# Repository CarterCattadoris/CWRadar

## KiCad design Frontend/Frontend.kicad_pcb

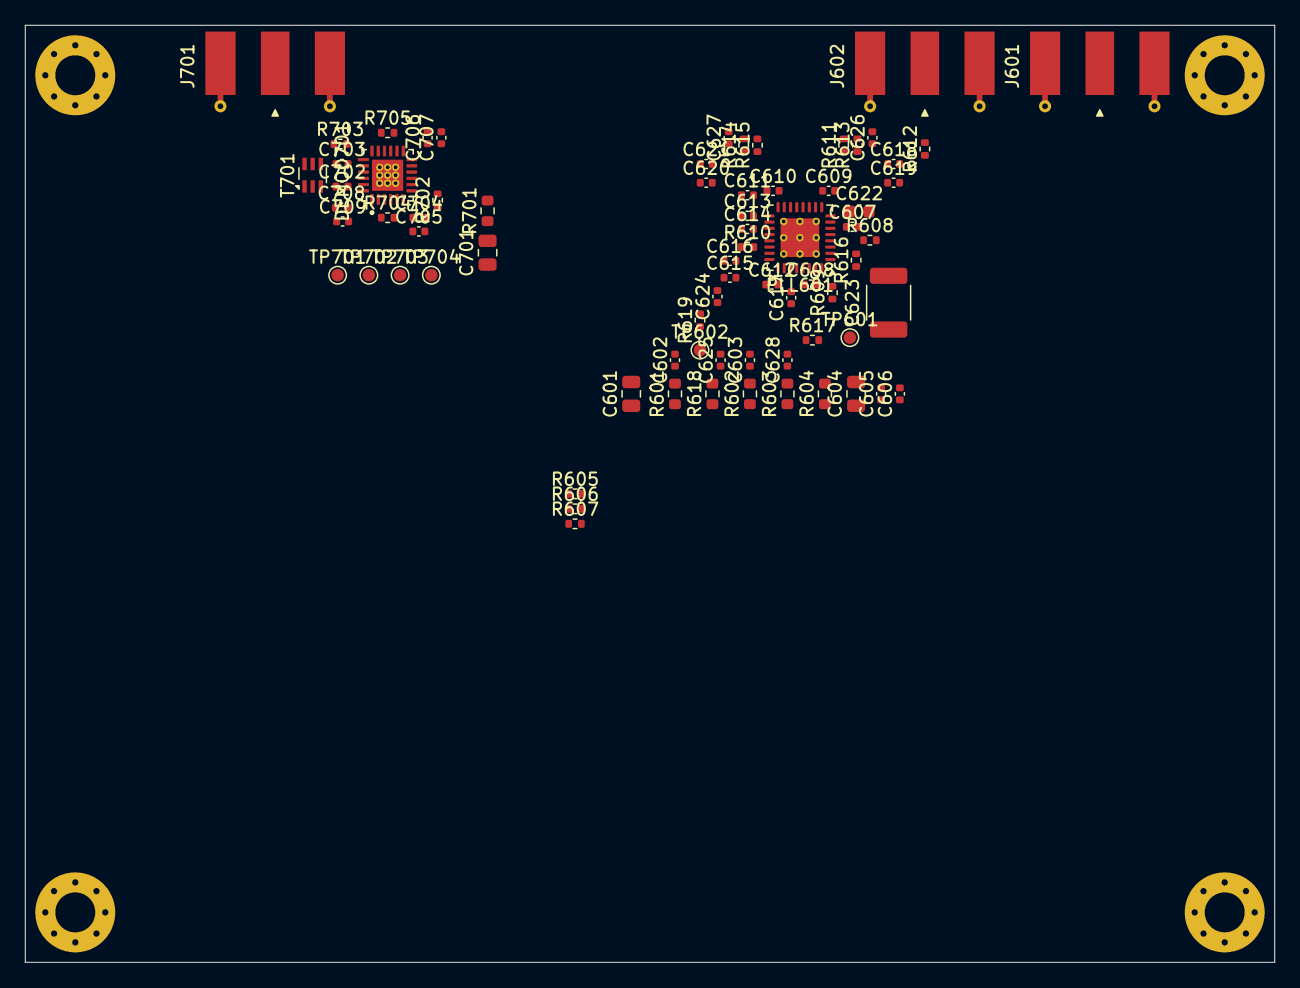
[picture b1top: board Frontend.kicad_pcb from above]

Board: 4 copper layers, 100.0 x 75.0 mm, 77 parts (0 on the bottom side), 42 nets, no tracks yet.

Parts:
C601, C604, C701: 10u; C_0805_2012Metric
C602, C603, C607, C608, C609, C611, C612, C613, C614, C615, C616, C625, C628: 1u; C_0402_1005Metric
C605, C705, C707, C709: 100n; C_0402_1005Metric
C606: 10n; C_0402_1005Metric
C610, C618, C619, C620, C621, C626, C627, C702, C703: TBD; C_0402_1005Metric
C617: 1n; C_0402_1005Metric
C622: 12n; C_0603_1608Metric
C623: 100n; C_Panasonic_ECHU_E2
C624: 820p; C_0402_1005Metric
C704, C706, C708: 100p; C_0402_1005Metric
DEMOD701: ADL5380; 24-WFQFN
J601: TX SMA; SMA_Molex_73251-1153_EdgeMount_Horizontal
J602: MON SMA; SMA_Molex_73251-1153_EdgeMount_Horizontal
J701: RX SMA; SMA_Molex_73251-1153_EdgeMount_Horizontal
MH1101, MH1102, MH1103, MH1104: M3; MountingHole_3.2mm_M3_Pad_Via
PLL601: MAX2871ETJ_T; TQFN-32-1EP_5x5mm_P0.5mm_EP3.1x3.1mm_ThermalVias0.3
R601, R602, R603, R618, R701: 0R; R_0603_1608Metric
R604: 10; R_0603_1608Metric
R605, R606, R607: 47; R_0402_1005Metric
R608, R609, R619: 100k; R_0402_1005Metric
R610: 5k1; R_0402_1005Metric
R611, R612, R613, R614, R615: 49R9; R_0402_1005Metric
R616: 120; R_0402_1005Metric
R617: 249; R_0402_1005Metric
R702: 0R; R_0402_1005Metric
R703: DNP (open >5 GHz); R_0402_1005Metric
R704, R705: DNP — diff load ≥500 Ω; R_0402_1005Metric
T701: 5400BL15B050; Balun_Johanson_5400BL15B050E
TP601: LD; TestPoint_Pad_D1.0mm
TP602: TUNE; TestPoint_Pad_D1.0mm
TP701: I_P; TestPoint_Pad_D1.0mm
TP702: I_N; TestPoint_Pad_D1.0mm
TP703: Q_N; TestPoint_Pad_D1.0mm
TP704: Q_P; TestPoint_Pad_D1.0mm

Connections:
+3V3_SYN: C601.1, R601.1, R602.1, R603.1, R604.1, R618.1
+3V3_SYN_DIG: C608.1, C612.1, C628.1, PLL601.28, PLL601.32, R603.2
+3V3_SYN_PLL: C603.1, C607.1, C609.1, PLL601.6, PLL601.10, R602.2
+3V3_SYN_REF: C604.1, C605.1, C606.1, R604.2
+3V3_SYN_RF: C602.1, C610.1, C611.1, C626.1, C627.1, PLL601.16, R601.2, R611.1, R613.1, R614.1, R615.1
+3V3_SYN_VCO: C613.1, C625.1, PLL601.17, R618.2
+5V_DEMOD: C701.1, C704.1, C705.1, C706.1, C707.1, C708.1, C709.1, DEMOD701.6, DEMOD701.13, DEMOD701.24, R701.2, R703.1
/Baseband_I/IN_N: DEMOD701.4, R704.2, TP702.1
/Baseband_I/IN_P: DEMOD701.3, R704.1, TP701.1
/Baseband_Q/IN_N: DEMOD701.15, R705.1, TP703.1
/Baseband_Q/IN_P: DEMOD701.16, R705.2, TP704.1
/Receiver/DEMOD_ADJ: DEMOD701.19, R703.2
/Receiver/DEMOD_ENBL: DEMOD701.7, R702.1
/Receiver/DEMOD_RFIN: C703.2, DEMOD701.21
/Receiver/DEMOD_RFIP: C702.2, DEMOD701.22
/Receiver/LO_N: C620.2, DEMOD701.9
/Receiver/LO_P: C621.2, DEMOD701.10
/Receiver/RX_BAL_N: C703.1, T701.4
/Receiver/RX_BAL_P: C702.1, T701.3
/Receiver/RX_RF: J701.1, T701.1
/Synthesizer/BIAS_FILT: C616.1, PLL601.23
/Synthesizer/CP_OUT: C622.1, PLL601.7, R616.1, R617.1
/Synthesizer/LF_C2: C623.1, R616.2
/Synthesizer/MON_RF: C618.2, J602.1, R612.1
/Synthesizer/NOISE_FILT: C614.1, PLL601.19
/Synthesizer/REF_IN: C617.2, PLL601.29
/Synthesizer/REG: C615.1, PLL601.24
/Synthesizer/RFOUTA_N: C618.1, PLL601.13, R611.2
/Synthesizer/RFOUTA_P: C619.1, PLL601.12, R613.2
/Synthesizer/RFOUTB_N: C620.1, PLL601.15, R614.2
/Synthesizer/RFOUTB_P: C621.1, PLL601.14, R615.2
/Synthesizer/RSET: PLL601.22, R610.1
/Synthesizer/SYN_CE: PLL601.4, R608.1
/Synthesizer/SYN_LD: PLL601.25, TP601.1
/Synthesizer/SYN_LE_R: PLL601.3, R607.2
/Synthesizer/SYN_MOSI_R: PLL601.2, R606.2
/Synthesizer/SYN_RFOUT_EN: PLL601.26, R609.1
/Synthesizer/SYN_SCK_R: PLL601.1, R605.2
/Synthesizer/TUNE: C624.1, PLL601.20, R617.2, R619.1
/Synthesizer/TUNE_TP: R619.2, TP602.1
/Synthesizer/TX_RF: C619.2, J601.1
GND: C601.2, C602.2, C603.2, C604.2, C605.2, C606.2, C607.2, C608.2, C609.2, C610.2, C611.2, C612.2, C613.2, C614.2, C615.2, C616.2, C622.2, C623.2, C624.2, C625.2, C626.2, C627.2, C628.2, C701.2, C704.2, C705.2, C706.2, C707.2, C708.2, C709.2, DEMOD701.1, DEMOD701.2, DEMOD701.5, DEMOD701.8, DEMOD701.11, DEMOD701.14, DEMOD701.17, DEMOD701.18, DEMOD701.20, DEMOD701.23, DEMOD701.25, DEMOD701.25_1, DEMOD701.25_2, DEMOD701.25_3, DEMOD701.25_4, DEMOD701.25_5, DEMOD701.25_6, DEMOD701.25_7, DEMOD701.25_8, DEMOD701.25_9, J601.2, J602.2, J701.2, MH1101.1, MH1102.1, MH1103.1, MH1104.1, PLL601.8, PLL601.9, PLL601.11, PLL601.18, PLL601.21, PLL601.27, PLL601.31, PLL601.33, R608.2, R609.2, R610.2, R612.2, R702.2, T701.2, T701.5

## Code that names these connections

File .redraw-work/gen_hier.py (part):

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    vpart(ref, "cwradar:100k", 40.64, y + 3.81)
    gnd(40.64, y + 7.62)
YLD = 184.15 + SH
hlabel("SYN_LD", 33.02, YLD, 180, "output")
wire((33.02, YLD), (48.26, YLD))
place("TP1", "Connector:TestPoint", 48.26, YLD, value="LD",
      fp="TestPoint:TestPoint_Pad_D1.0mm",
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
# ============================================================== LOOP FILTER
Y0 = 214.63 + SH
label("CP_OUT", 22.86, Y0, 180)
wire((22.86, Y0), (52.07, Y0))
vpart("C22", "cwradar:12n", 33.02, Y0 + 3.81); gnd(33.02, Y0 + 7.62)
vpart("R16", "cwradar:120", 43.18, Y0 + 3.81)
wire((43.18, Y0 + 7.62), (43.18, Y0 + 10.16))
label("LF_C2", 43.18, Y0 + 8.89, 90, small=True)
vpart("C23", "cwradar:100n_PPS", 43.18, Y0 + 13.97); gnd(43.18, Y0 + 17.78)
hpart("R17", "cwradar:249", 55.88, Y0)
wire((59.69, Y0), (78.74, Y0))
vpart("C24", "cwradar:820p", 66.04, Y0 + 3.81); gnd(66.04, Y0 + 7.62)
label("TUNE", 73.66, Y0, 0)
# TUNE probe point: 100k keeps probe capacitance off the loop filter
vpart("R19", "cwradar:100k", 78.74, Y0 + 3.81,
      extra={"Note": "Isolates probe capacitance from loop filter. Place R at the TUNE node."})
wire((78.74, Y0 + 7.62), (78.74, Y0 + 10.16))
label("TUNE_TP", 78.74, Y0 + 8.89, 90, small=True)
place("TP2", "Connector:TestPoint", 78.74, Y0 + 10.16, rot=180, value="TUNE",
      fp="TestPoint:TestPoint_Pad_D1.0mm",
      fields={"Reference": (81.28, Y0 + 12.7, 0, False, "right"), "Value": (81.28, Y0 + 15.24, 0, False, "right")})
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R = P["6"][0]   # right pin x

# left-side control/status labels
for pin, net in [("4", "SYN_CE"), ("1", "SYN_SCK_R"), ("2", "SYN_MOSI_R"),
                 ("3", "SYN_LE_R"), ("20", "TUNE")]:
    label(net, *P[pin], 180)
NCS.append(P["5"])
# right-side labels
for pin, net in [("26", "SYN_RFOUT_EN"), ("7", "CP_OUT"), ("25", "SYN_LD"),
                 ]:
    label(net, *P[pin], 0)
hlabel("SYN_MISO", *P["30"], 0, "output")
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
# VCO / bias decoupling and RSET: staircase down-left
YB = 165.1
for pin, cref, part, cx, net in [("23", "C16", "cwradar:1u", 127.0, "BIAS_FILT"),
                                 ("24", "C15", "cwradar:1u", 116.84, "REG"),
                                 ("19", "C14", "cwradar:1u", 106.68, "NOISE_FILT"),
                                 ("22", "R10", "cwradar:5k1", 96.52, "RSET")]:
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hpart("C17", "cwradar:1n", 125.73, ry,
      fields={"Reference": (125.73, ry - 2.794, 90, False), "Value": (125.73, ry + 3.175, 90, False)})
wire(P["29"], (129.54, ry))
label("REF_IN", 130.81, ry, 0, small=True)
label("REF_25M", 121.92, ry, 180)

# reference TCXO placeholder (part TBD), on the RC-filtered +3V3_SYN_REF branch
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    hpart(cref, "Device:C", DCB, Y, value="TBD", fp="Capacitor_SMD:C_0402_1005Metric")
    if net == "RFOUTA_P":
        wire((DCB + 3.81, Y), (J - 5.08, Y))
        label("TX_RF", DCB + 5.08, Y, 0, small=True)
        place("J1", "Connector:Conn_Coaxial", J, Y, value="TX SMA", fp="Connector_Coaxial:SMA_Molex_73251-1153_EdgeMount_Horizontal", extra={"Manufacturer": "Molex", "Mfg Part #": "73251-1153", "Description": "SMA jack, edge mount, 1.6 mm PCB"},
              fields={"Reference": (J + 3.81, Y - 2.54, 0, False, "left"),
                      "Value": (J + 3.81, Y, 0, False, "left")})
        gnd(J, Y + 5.08)
    elif net == "RFOUTA_N":
        wire((DCB + 3.81, Y), (J - 5.08, Y))
        label("MON_RF", DCB + 5.08, Y, 0, small=True)
        vpart("R12", "cwradar:49R9", 238.76, Y + 3.81); gnd(238.76, Y + 7.62)
        place("J2", "Connector:Conn_Coaxial", J, Y, value="MON SMA",
              fp="Connector_Coaxial:SMA_Molex_73251-1153_EdgeMount_Horizontal", dnp=True, extra={"Manufacturer": "Molex", "Mfg Part #": "73251-1153", "Description": "SMA jack, edge mount, 1.6 mm PCB"},
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
# ===================================================================== notes
text("MAX2871 NOTES (DS Rev 4)\n"
     "- One 1u 10V X5R 0402 on every supply pin (C7-C9, C11-C13), branch caps C2/C3 and NOISE_FILT/BIAS_FILT/REG (C14-C16).\n"
     "  Place each 1u directly at its pin, own GND via at or in the pad. Check the part's DC-bias curve at 3.3V; no Y5V.\n"
     "- C10: C0G 0402 on VCC_RF, series-resonant at 5.8 GHz when mounted (~1-3 pF, from vendor S-params), closest to pin 16.\n"
     "- C18-C21 DC blocks: 0402 C0G near series resonance at 5.8 GHz. R5-R7 47R series: place at the ESP32 end.\n"
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          fields={"Reference": (129.54, 114.3, 0, False), "Value": (129.54, 116.84, 0, False)})
assert T["4"] == (134.62, YN) and T["3"] == (134.62, YP), T
wire(J["1"], T["1"])
label("RX_RF", 109.22, YP, 0, small=True)
gx2, gy2 = T["2"]  # GND pins face up on the mirrored balun
wire((gx2, gy2), (gx2, gy2 - 2.54), (gx2 - 5.08, gy2 - 2.54), (gx2 - 5.08, gy2))
gnd(gx2 - 5.08, gy2)
# balanced polarity chosen for a crossing-free layout (RF inversion flips I and Q together)
for tp, bal, cref, dem, pin in [("3", "RX_BAL_P", "C2", "DEMOD_RFIP", "22"),
                                ("4", "RX_BAL_N", "C3", "DEMOD_RFIN", "21")]:
    y = T[tp][1]
    wire(T[tp], (153.67, y))
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
# LO in: already AC-coupled on the synthesizer sheet (C620/C621). LO_P -> LOIN so the pair
# routes without crossing; LO inversion flips I and Q together, so the Doppler sign is unchanged.
for pin, lo in [("10", "LO_P"), ("9", "LO_N")]:
    px, py = D[pin]
    hlabel(lo, 160.02, py, 180, "input")
    wire((160.02, py), (px, py))
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# ADJ: open above 5 GHz, DNP footprint to VS for IIP3 tuning
ax, ay = D["19"]
wire((142.24, ay), (ax, ay))
label("DEMOD_ADJ", 162.56, ay, 0, small=True)
hpart("R3", "Device:R", 138.43, ay, value="DNP (open >5 GHz)", fp="Resistor_SMD:R_0402_1005Metric",
      dnp=True, fields={"Reference": (138.43, ay + 3.81, 90, False), "Value": (138.43, ay + 6.35, 90, False)})
rail("+5V_DEMOD", 134.62, ay)
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# ENBL low = enabled; 0R so the trace can move to an MCU GPIO later
ex, ey = D["7"]
wire((152.4, ey), (ex, ey))
label("DEMOD_ENBL", 162.56, ey, 0, small=True)
vpart("R2", "cwradar:0R_0402", 152.4, ey + 3.81)
gnd(152.4, ey + 7.62)
NCS.append(D["12"])
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     "  Keep balun-to-pin traces < ~1.4 mm and symmetric.\n"
     "- LO: LO_P/LO_N already AC-coupled on MAX2871 sheet (C620/C621). No second DC block.\n"
     "- BB out: 50 Ω diff, CM ≈ VS-1.2 V with ADJ open. DNP diff load per pair. I/Q mapping: IHI(3)->I_P, ILO(4)->I_N,\n"
     "  QHI(16)->Q_P, QLO(15)->Q_N. RF: T701 pin 3 -> RX_BAL_P -> RFIP(22), pin 4 -> RX_BAL_N -> RFIN(21).\n"
     "  LO: LO_P -> LOIN(10), LO_N -> LOIP(9) (RF and LO polarity picked for crossing-free routing).\n"
     "  Swapping the I or the Q pair (not both) flips the Doppler sign;\n"
     "  swapping the RF or LO pair inverts I and Q together and does not.\n"
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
